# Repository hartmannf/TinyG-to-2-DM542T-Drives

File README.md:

# TinyG-to-2-DM542T-Drives
TinyG to 2 DM542T Driver 12/24V Version

Original Idee was to connect on the TinyG v8 2 external stepperdriver of type DM542T to connect 2 Nema 23 on it. 
Thanks to Carl McGrath

Dokuments: 
Overview_TinyG_DM542T.pdf --> Typical application overview
DM542_PCB.PNG --> PCB view
DM542_PCB_top_Comp_.PNG --> Top View Components
DM542_SCH.PNG --> Schematic view
DM542T_Specification.pdf --> Driver Specification
Eagle_files
  --> DM542T.brd
  --> DM542T.SCH
  --> Eagle.epf
  
Function: 
Connect to tinyg v8 "Step, DIR,ENA" power with 12V from tinyg or 24V to where also the 2 DM542T Drivers are powered. with Jumpers switch Voltage can be be selected. 

Connection:
Connector: xTinyG to TinyG Board 
  12VDC -->  FAN 12VDC
  GND --> GND
  STEP --> STEP (Motor 1...4)
  DIR --> DIR (Motor 1...4)
  ENA --> ENABLE (Motor 1...4)

Connector: 24V1 .. 24V4
  GND --> Powersupply Ground
  24V1 --> Powersupply 24VDC

Connector for Drive 1 and 2:
  Pul+ --> Pul+
  Pul- --> Pul-
  DIR+ --> DIR+
  DIR- --> DIR-
  ENA+ --> ENA+
  ENA- --> ENA-
  
Voltage Selector
  JP12/24 selects the Power Source 12V if powered by TinyG or 24V if Powered with same Powersource like DM542T 
  JP12.1 .. JP12.6 if 12V Powerd from TinyG
  JP24.1 .. JP24.6 if Powered same then DM542T 
  BE AWARE OF: Power Source can only be either 12V or 24V.

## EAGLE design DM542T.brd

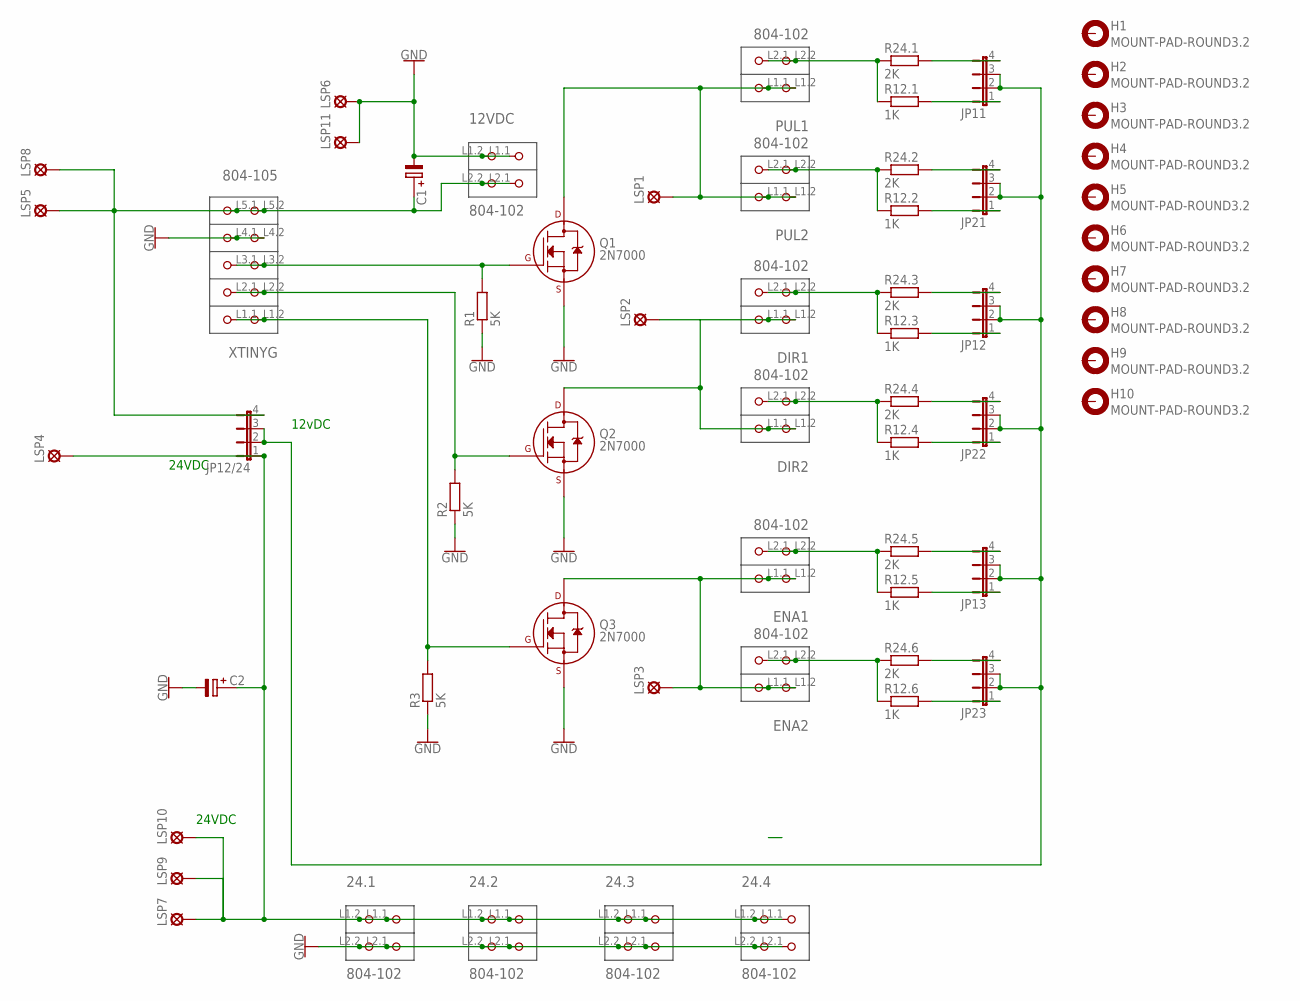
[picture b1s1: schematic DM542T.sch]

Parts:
12VDC, 24.1, 24.2, 24.3, 24.4: 804-102; P-804-102
C1, C2: C-PR-3,5X10; E3,5-10
DIR1, DIR2: 804-102; P-804-102
ENA1, ENA2: 804-102; P-804-102
H1, H2, H3, H4, H5, H6, H7, H8, H9, H10: MOUNT-PAD-ROUND3.2; 3,2-PAD
JP11, JP12, JP12/24, JP13, JP21, JP22, JP23: JP4E; JP4
LSP1, LSP2, LSP3, LSP4, LSP5, LSP6, LSP7, LSP8, LSP9, LSP10, LSP11: LSP10
PUL1, PUL2: 804-102; P-804-102
Q1, Q2, Q3: 2N7000; TO-92
R1, R2, R3: 5K; 0207/15
R12.1, R12.2, R12.3, R12.4, R12.5, R12.6: 1K; 0207/15
R24.1, R24.2, R24.3, R24.4, R24.5, R24.6: 2K; 0207/15
XTINYG: 804-105; P-804-105

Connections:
GND: 12VDC.L1.1 (P1.1), 12VDC.L1.2 (P1.2), 24.1.L2.1 (P2.1), 24.1.L2.2 (P2.2), 24.2.L2.1 (P2.1), 24.2.L2.2 (P2.2), 24.3.L2.1 (P2.1), 24.3.L2.2 (P2.2), 24.4.L2.1 (P2.1), 24.4.L2.2 (P2.2), C1.-, C2.-, LSP6.MP, LSP11.MP, Q1.1 (S), Q2.1 (S), Q3.1 (S), R1.1, R2.1, R3.1, XTINYG.L4.1 (P4.1), XTINYG.L4.2 (P4.2)
unnamed: PUL1.L2.1 (P2.1), PUL1.L2.2 (P2.2), R12.1.1, R24.1.1
unnamed: 12VDC.L2.1 (P2.1), 12VDC.L2.2 (P2.2), C1.+, JP12/24.4, LSP5.MP, LSP8.MP, XTINYG.L5.1 (P5.1), XTINYG.L5.2 (P5.2)
unnamed: Q2.2 (G), R2.2, XTINYG.L2.1 (P2.1), XTINYG.L2.2 (P2.2)
unnamed: Q3.2 (G), R3.2, XTINYG.L1.1 (P1.1), XTINYG.L1.2 (P1.2)
unnamed: DIR1.L1.1 (P1.1), DIR1.L1.2 (P1.2), DIR2.L1.1 (P1.1), DIR2.L1.2 (P1.2), LSP2.MP, Q2.3 (D)
unnamed: 24.1.L1.1 (P1.1), 24.1.L1.2 (P1.2), 24.2.L1.1 (P1.1), 24.2.L1.2 (P1.2), 24.3.L1.1 (P1.1), 24.3.L1.2 (P1.2), 24.4.L1.1 (P1.1), 24.4.L1.2 (P1.2), C2.+, JP12/24.1, LSP4.MP, LSP7.MP, LSP9.MP, LSP10.MP
unnamed: JP11.4, R24.1.2
unnamed: LSP1.MP, PUL1.L1.1 (P1.1), PUL1.L1.2 (P1.2), PUL2.L1.1 (P1.1), PUL2.L1.2 (P1.2), Q1.3 (D)
unnamed: PUL2.L2.1 (P2.1), PUL2.L2.2 (P2.2), R12.2.1, R24.2.1
unnamed: JP11.1, R12.1.2
unnamed: JP13.4, R24.5.2
unnamed: JP12.1, R12.3.2
unnamed: JP22.4, R24.4.2
unnamed: JP13.1, R12.5.2
unnamed: DIR1.L2.1 (P2.1), DIR1.L2.2 (P2.2), R12.3.1, R24.3.1
unnamed: JP11.2, JP11.3, JP12.2, JP12.3, JP12/24.2, JP12/24.3, JP13.2, JP13.3, JP21.2, JP21.3, JP22.2, JP22.3, JP23.2, JP23.3
unnamed: JP12.4, R24.3.2
unnamed: ENA1.L2.1 (P2.1), ENA1.L2.2 (P2.2), R12.5.1, R24.5.1
unnamed: JP21.1, R12.2.2
unnamed: JP23.4, R24.6.2
unnamed: JP23.1, R12.6.2
unnamed: ENA2.L2.1 (P2.1), ENA2.L2.2 (P2.2), R12.6.1, R24.6.1
unnamed: JP21.4, R24.2.2
unnamed: ENA1.L1.1 (P1.1), ENA1.L1.2 (P1.2), ENA2.L1.1 (P1.1), ENA2.L1.2 (P1.2), LSP3.MP, Q3.3 (D)
unnamed: DIR2.L2.1 (P2.1), DIR2.L2.2 (P2.2), R12.4.1, R24.4.1
unnamed: JP22.1, R12.4.2
unnamed: Q1.2 (G), R1.2, XTINYG.L3.1 (P3.1), XTINYG.L3.2 (P3.2)

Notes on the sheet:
12vDC
24VDC

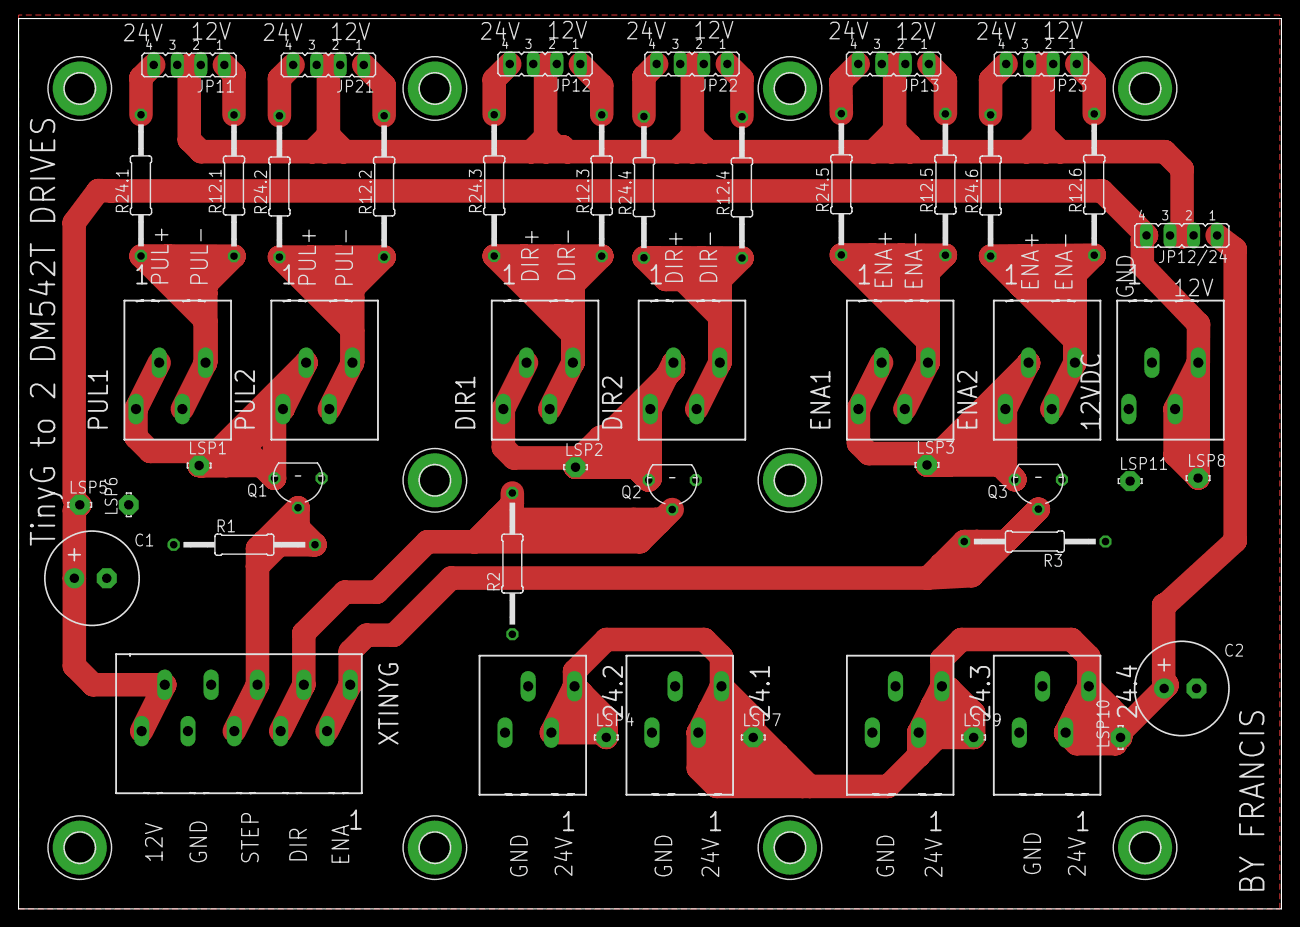
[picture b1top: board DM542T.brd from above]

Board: 2 copper layers, 136.2 x 96.0 mm, 60 parts (0 on the bottom side), 28 nets.

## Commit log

2018-10-12 Add files via upload
    Fritzing file to manufacture by Aisle

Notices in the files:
parts and their libraries:
cap-pan40: Copyright (C) 2004, Bob Starr
SparkFun-PowerSymbols: Licensing: Creative Commons ShareAlike 4.0 International - https://creativecommons.org/licenses/by-sa/4.0
